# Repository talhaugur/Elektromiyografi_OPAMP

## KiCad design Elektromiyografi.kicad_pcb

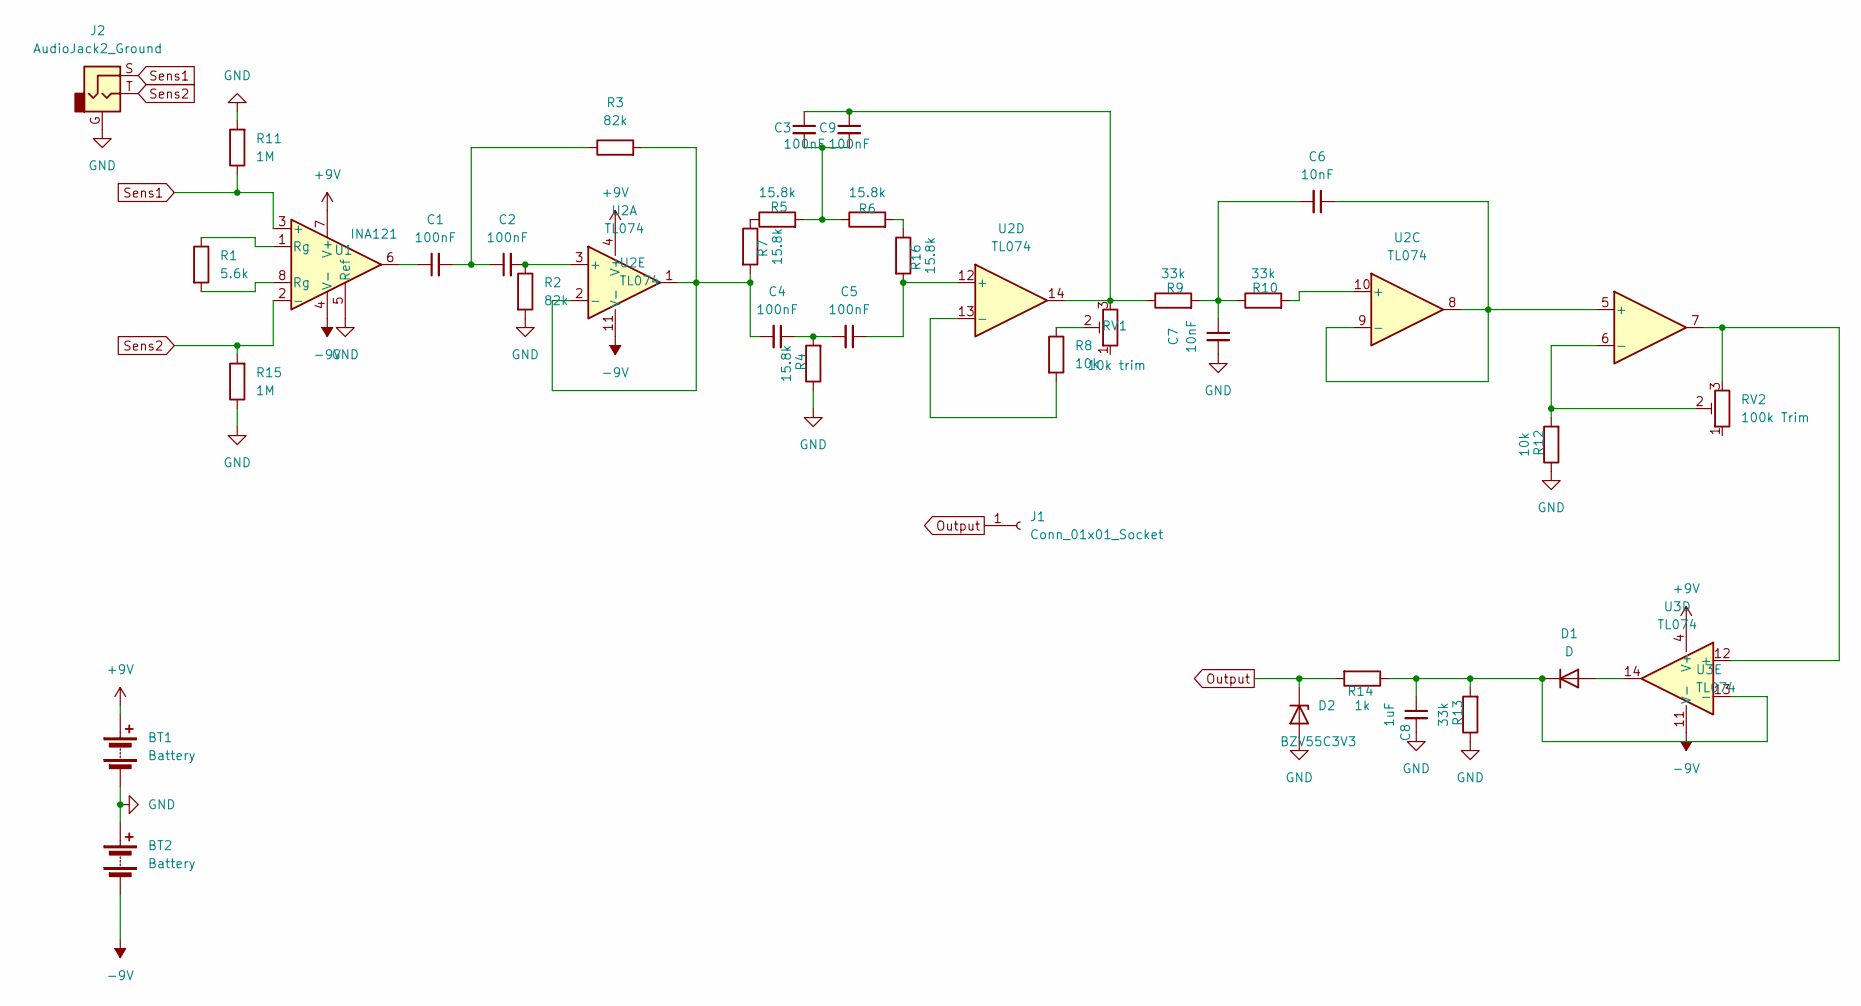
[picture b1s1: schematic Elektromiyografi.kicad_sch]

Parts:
BT1, BT2: Battery; BatteryHolder_Eagle_12BH611-GR
C1, C2, C3, C4, C5, C9: 100nF; C_0603_1608Metric_Pad1.08x0.95mm_HandSolder
C6, C7: 10nF; C_0603_1608Metric_Pad1.08x0.95mm_HandSolder
C8: 1uF; C_0603_1608Metric_Pad1.08x0.95mm_HandSolder
D1: D; D_0603_1608Metric
D2: BZV55C3V3; D_MiniMELF
J1: Conn_01x01_Socket; JWT_A3963_1x02_P3.96mm_Vertical
J2: AudioJack2_Ground; Jack_3.5mm_Switronic_ST-005-G_horizontal
R1: 5.6k; R_0603_1608Metric_Pad0.98x0.95mm_HandSolder
R2, R3: 82k; R_0603_1608Metric_Pad0.98x0.95mm_HandSolder
R4, R5, R6, R7, R16: 15.8k; R_0603_1608Metric_Pad0.98x0.95mm_HandSolder
R8, R12: 10k; R_0603_1608Metric_Pad0.98x0.95mm_HandSolder
R9, R10, R13: 33k; R_0603_1608Metric_Pad0.98x0.95mm_HandSolder
R11, R15: 1M; R_0603_1608Metric_Pad0.98x0.95mm_HandSolder
R14: 1k; R_0603_1608Metric_Pad0.98x0.95mm_HandSolder
RV1: 10k trim; Potentiometer_Runtron_RM-065_Vertical
RV2: 100k Trim; Potentiometer_Runtron_RM-065_Vertical
U1: INA121; DIP-8_W7.62mm_Socket
U2: TL074; DIP-14_W7.62mm_Socket
U3: TL074

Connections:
+9V: BT1.1 (+), U1.7 (V+), U2.4 (V+), U3.4 (V+)
-9V: BT2.2 (-), U1.4 (V-), U2.11 (V-), U3.11 (V-)
GND: BT1.2 (-), BT2.1 (+), C7.2, C8.2, D2.2 (A), J2.G, R2.2, R4.1, R11.2, R12.1, R13.1, R15.1, U1.5 (Ref)
unnamed: C1.1, U1.6
unnamed: C1.2, C2.1, R3.1
unnamed: C3.1, C9.1, R9.1, RV1.3, U2.14
unnamed: C3.2, C9.2, R5.2, R6.1
unnamed: C4.1, C5.2, R4.2
unnamed: C6.2, C7.1, R9.2, R10.1
unnamed: D1.2 (A), U3.14
unnamed: C8.1, D1.1 (K), R13.2, R14.1, U3.13 (-)
unnamed: R1.1, U1.1 (Rg)
unnamed: R1.2, U1.8 (Rg)
unnamed: R5.1, R7.1
unnamed: R8.1, RV1.2
unnamed: R6.2, R16.1
unnamed: C2.2, R2.1, U2.3 (+)
unnamed: C4.2, R3.2, R7.2, U2.1, U2.2 (-)
unnamed: C6.1, U2.5 (+), U2.8, U2.9 (-)
unnamed: R12.2, RV2.2, U2.6 (-)
unnamed: R10.2, U2.10 (+)
unnamed: C5.1, R16.2, U2.12 (+)
unnamed: R8.2, U2.13 (-)
unnamed: RV2.3, U2.7, U3.12 (+)
Output: D2.1 (K), J1.1, R14.2
Sens1: J2.S, R11.1, U1.3 (+)
Sens2: J2.T, R15.2, U1.2 (-)

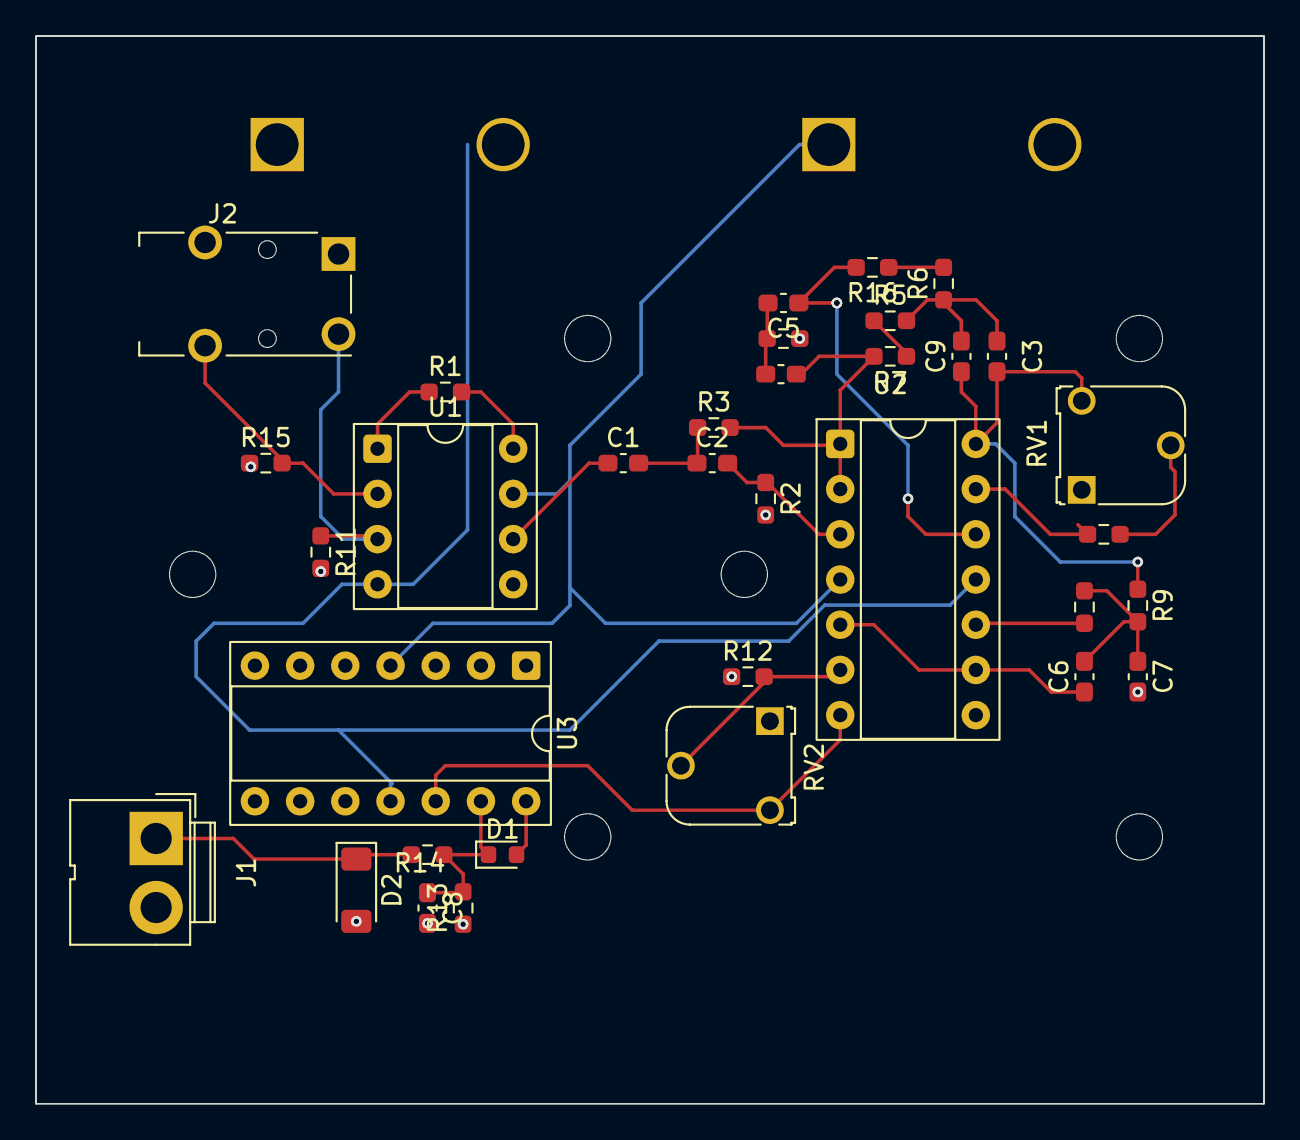
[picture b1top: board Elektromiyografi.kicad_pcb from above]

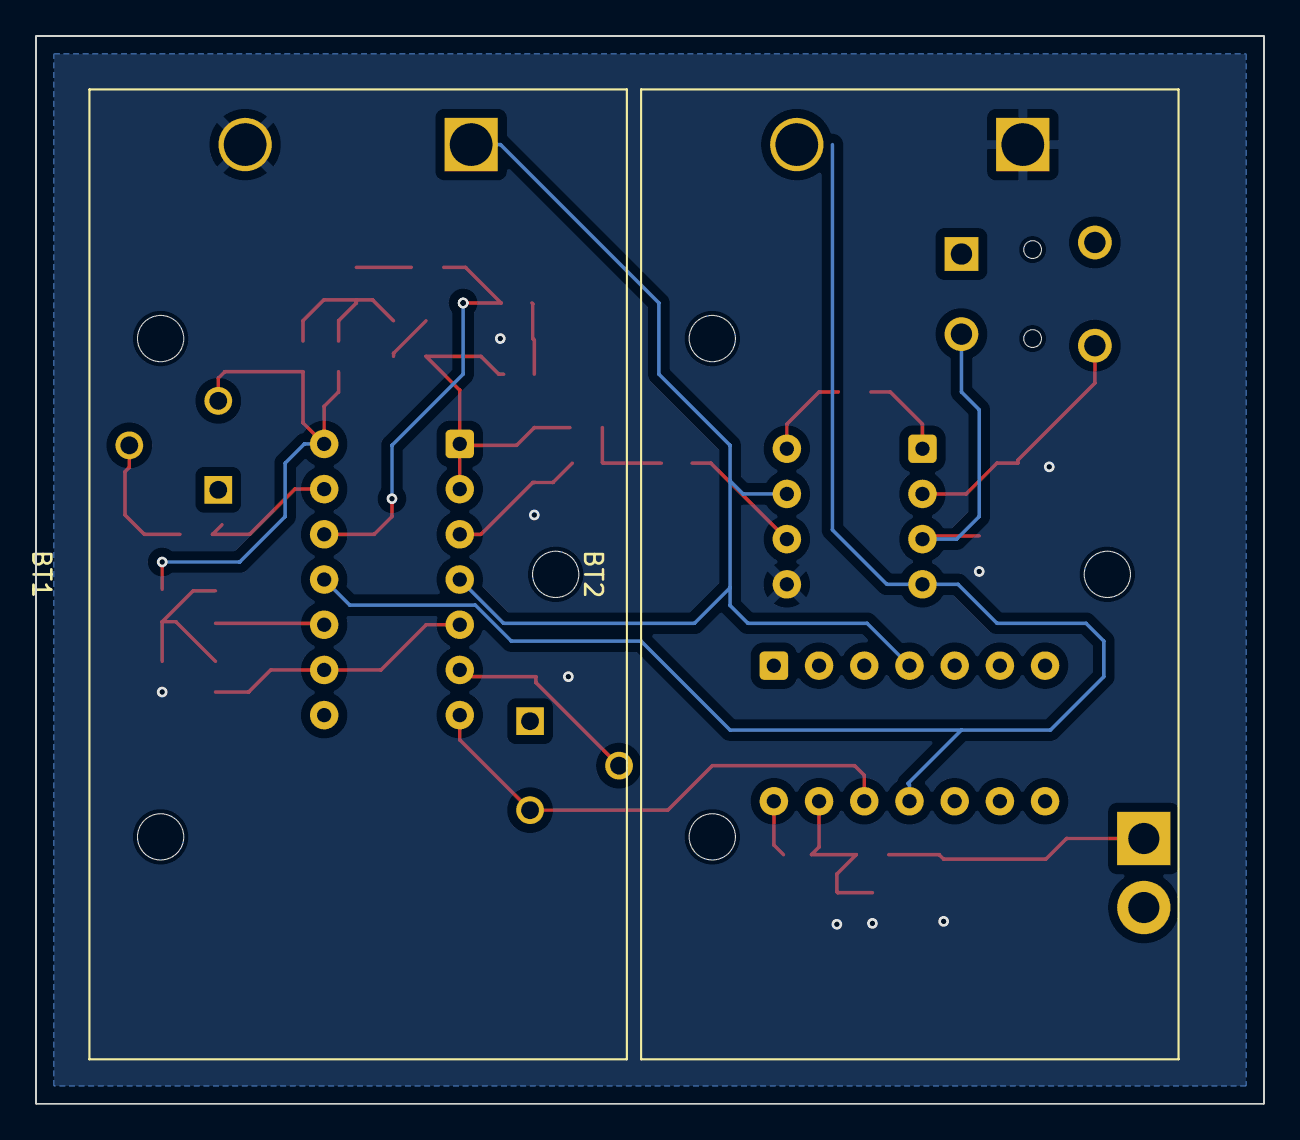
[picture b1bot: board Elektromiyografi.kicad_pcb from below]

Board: 2 copper layers, 69.0 x 60.0 mm, 36 parts (2 on the bottom side), 27 nets.
